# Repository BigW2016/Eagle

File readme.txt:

lfuse:0xE2
hfuse:0xDF
efuse:0xF9

F5mm 5mm Round Ultra Violet UV LED 3.2-3.4V 20mA 395nm - 400nm For DIY
Plastic Nylon Hex Column M3*12mm
Plastic Screw M3*6mm
Plastic Knob for Rotary Taper Potentiometer Hole 6mm - drilled for 6mm

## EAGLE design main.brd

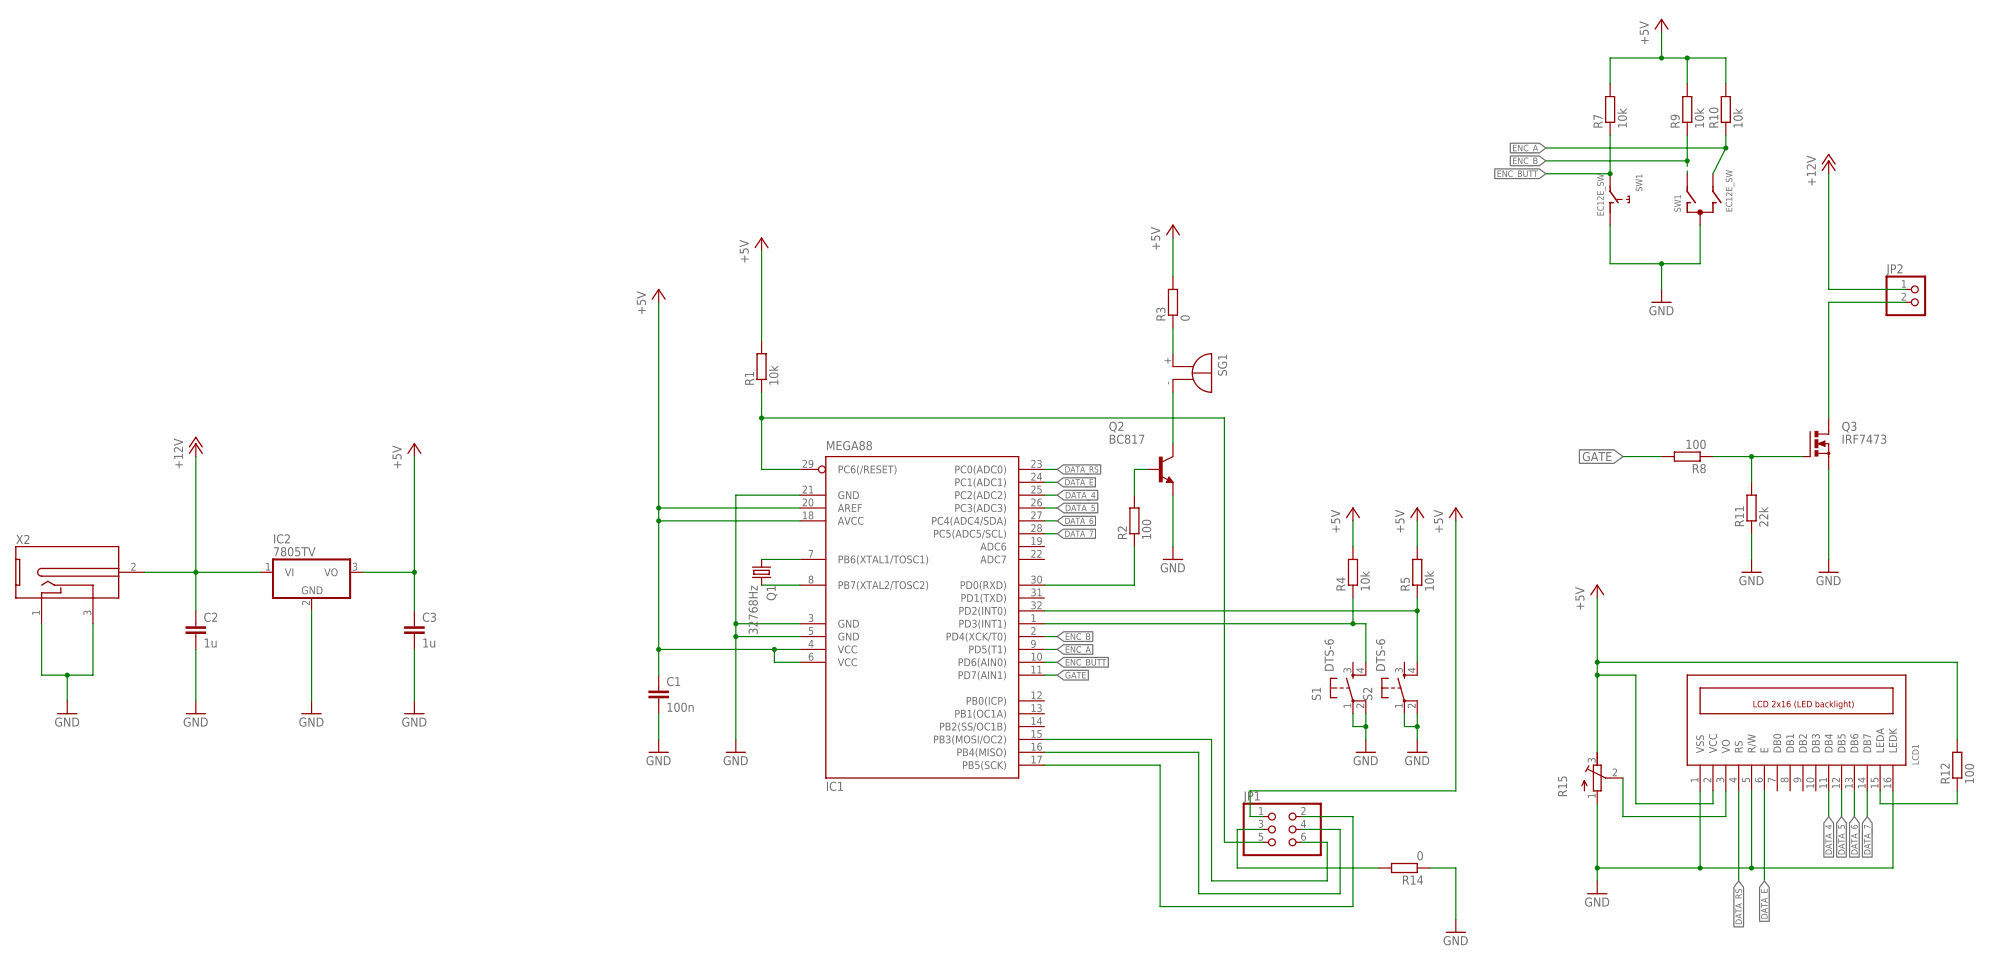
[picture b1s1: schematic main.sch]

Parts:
C1: 100n; C1206K
C2, C3: 1u; C1206K
IC1: MEGA88; TQFP32-08
IC2: 7805TV; TO220V
JP1: PINHD-2X3; 2X03
JP2: PINHD-1X2; 1X02
LCD1: LCD_2X16_SIL; HY-1602F
Q1: 32768Hz; TC38H
Q2: BC817; SOT23-BEC
Q3: IRF7473; SO-08
R1, R4, R5, R7, R9, R10: 10k; R1206
R2, R8, R12: 100; R1206
R3, R14: 0; R1206
R11: 22k; R1206
R15: R-TRIMM3296W; RTRIM3296W
S1, S2: DTS-6
SG1: BMT1205XH7.5
SW1: EC12E_SW; ALPS_EC12E_SW
X2: DC-2.5MM-5MM; DC-21MM

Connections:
+5V: C1.1, C3.1, IC1.4 (VCC), IC1.6 (VCC), IC1.18 (AVCC), IC1.20 (AREF), IC2.3 (VO), JP1.1, LCD1.2 (VCC), R1.2, R3.2, R4.2, R5.2, R7.2, R9.2, R10.2, R12.2, R15.3 (E)
+12V: C2.1, IC2.1 (VI), JP2.1, X2.2 (3)
DATA_4: IC1.25 (PC2(ADC2)), LCD1.11 (DB4)
DATA_5: IC1.26 (PC3(ADC3)), LCD1.12 (DB5)
DATA_6: IC1.27 (PC4(ADC4/SDA)), LCD1.13 (DB6)
DATA_7: IC1.28 (PC5(ADC5/SCL)), LCD1.14 (DB7)
DATA_E: IC1.24 (PC1(ADC1)), LCD1.6 (E)
DATA_RS: IC1.23 (PC0(ADC0)), LCD1.4 (RS)
ENC_A: IC1.9 (PD5(T1)), R10.1, SW1.B
ENC_B: IC1.2 (PD4(XCK/T0)), R9.1, SW1.A
ENC_BUTT: IC1.10 (PD6(AIN0)), R7.1, SW1.E (BUTT)
GATE: IC1.11 (PD7(AIN1)), R8.2
GND: C1.2, C2.2, C3.2, IC1.3 (GND), IC1.5 (GND), IC1.21 (GND), IC2.2 (GND), LCD1.1 (VSS), LCD1.5 (R/W), LCD1.16 (LEDK), Q2.E, Q3.1 (S), Q3.2 (S), Q3.3 (S), R11.1, R14.1, R15.1 (A), S1.1, S1.2, S2.1, S2.2, SW1.C, SW1.GND@1 (BUTT_GND), X2.1, X2.3 (2)
unnamed: IC1.17 (PB5(SCK)), JP1.2
unnamed: JP1.3, R14.2
unnamed: IC1.15 (PB3(MOSI/OC2)), JP1.6
unnamed: Q3.4 (G), R8.1, R11.2
unnamed: IC1.16 (PB4(MISO)), JP1.4
unnamed: IC1.29 (PC6(/RESET)), JP1.5, R1.1
unnamed: IC1.30 (PD0(RXD)), R2.1
unnamed: Q2.C, SG1.-
unnamed: Q2.B, R2.2
unnamed: R3.1, SG1.+
unnamed: JP2.2, Q3.5 (D), Q3.6 (D), Q3.7 (D), Q3.8 (D)
unnamed: IC1.7 (PB6(XTAL1/TOSC1)), Q1.1
unnamed: IC1.8 (PB7(XTAL2/TOSC2)), Q1.2
unnamed: IC1.32 (PD2(INT0)), R5.1, S2.4
unnamed: IC1.1 (PD3(INT1)), R4.1, S1.4
unnamed: LCD1.3 (VO), R15.2 (S)
unnamed: LCD1.15 (LEDA), R12.1

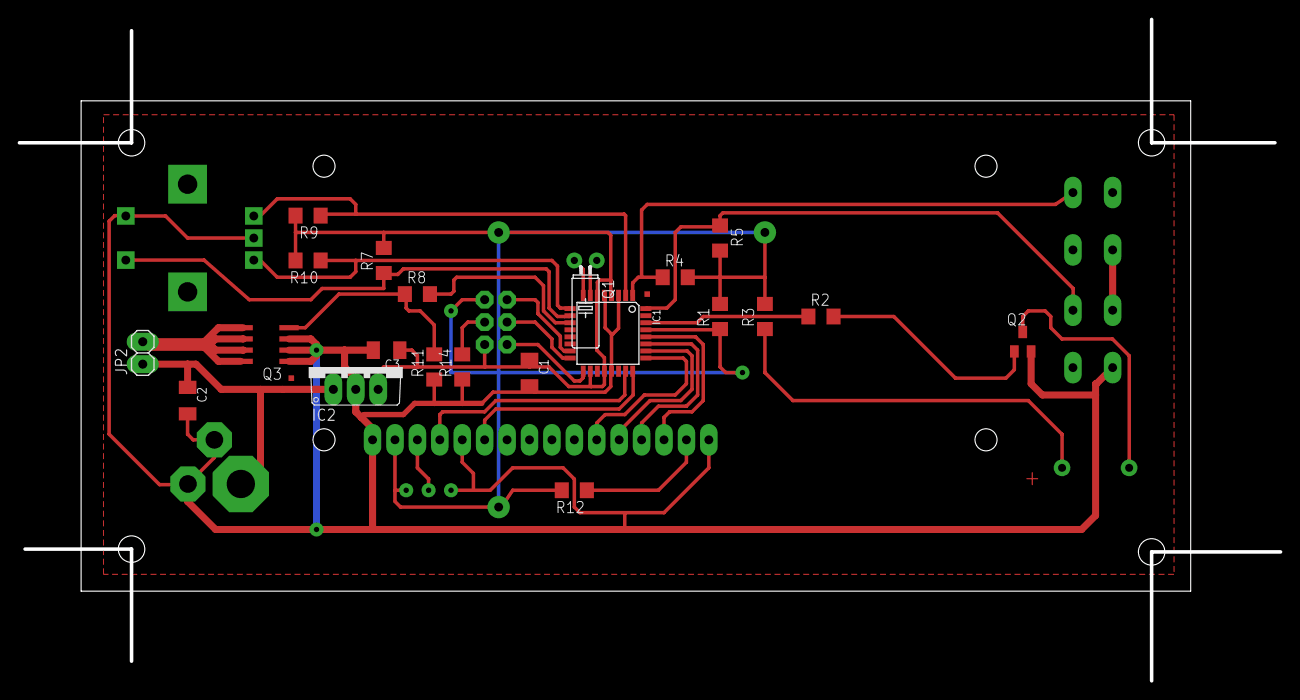
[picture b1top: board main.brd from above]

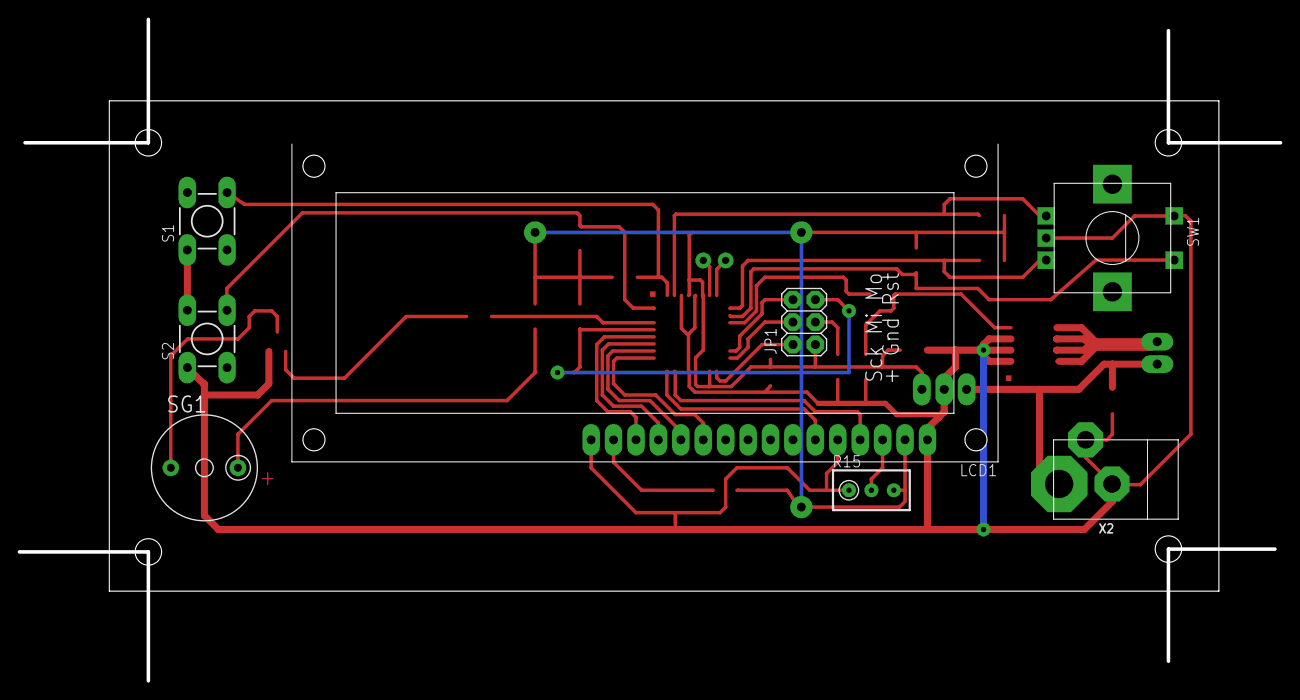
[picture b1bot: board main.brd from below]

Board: 2 copper layers, 142.9 x 74.9 mm, 29 parts (8 on the bottom side), 30 nets.

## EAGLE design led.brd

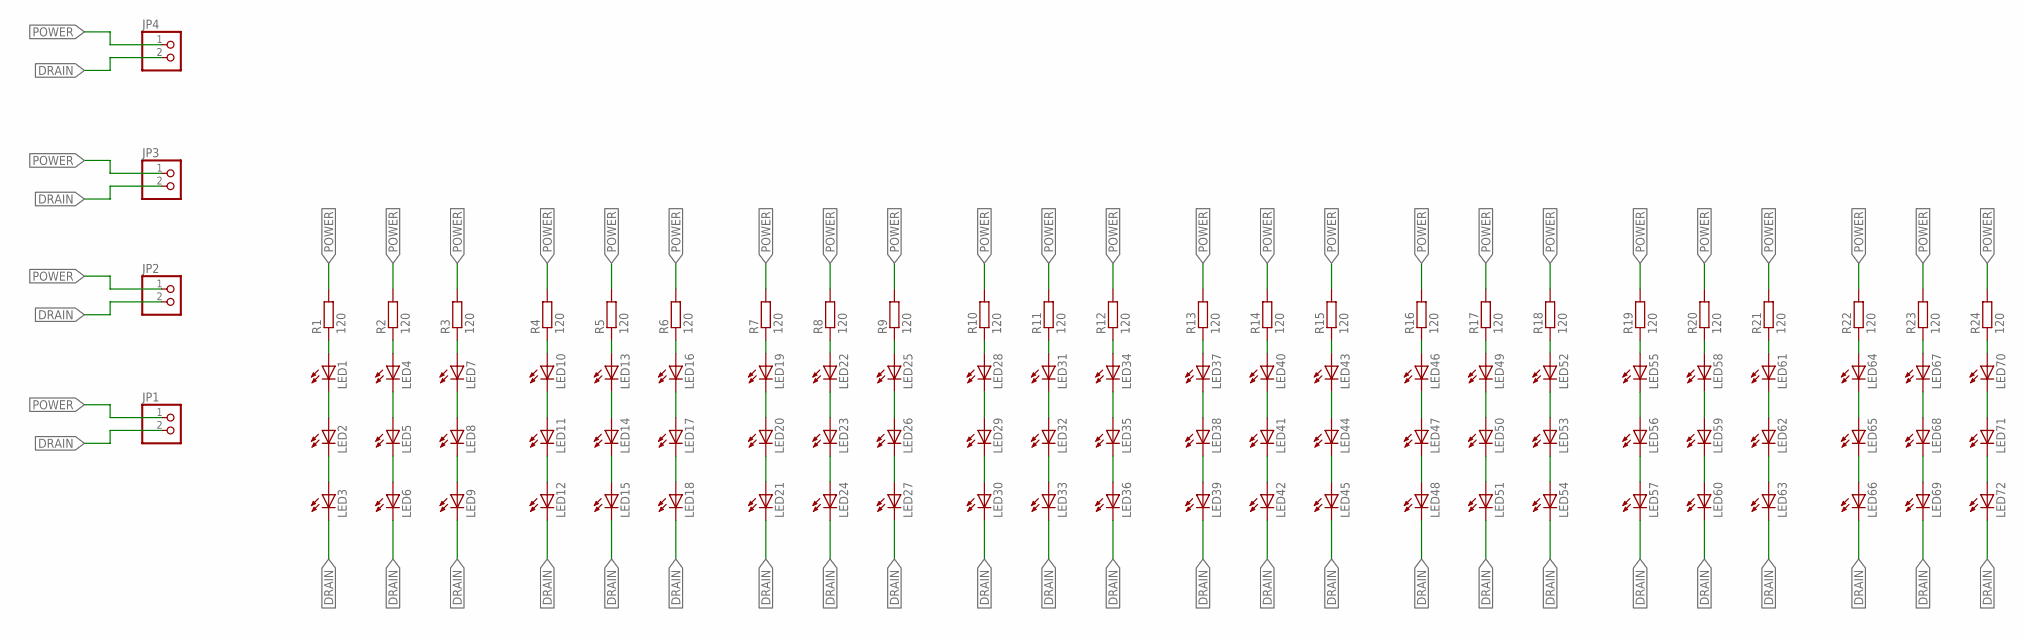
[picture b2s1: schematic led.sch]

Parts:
JP1, JP2, JP3, JP4: PINHD-1X2; 1X02
LED1, LED2, LED3, LED4, LED5, LED6, LED7, LED8, LED9, LED10, LED11, LED12, LED13, LED14, LED15, LED16, LED17, LED18, LED19, LED20, LED21, LED22, LED23, LED24, LED25, LED26, LED27, LED28, LED29, LED30, LED31, LED32, LED33, LED34, LED35, LED36, LED37, LED38, LED39, LED40, LED41, LED42, LED43, LED44, LED45, LED46, LED47, LED48, LED49, LED50, LED51, LED52, LED53, LED54, LED55, LED56, LED57, LED58, LED59, LED60, LED61, LED62, LED63, LED64, LED65, LED66, LED67, LED68, LED69, LED70, LED71, LED72: LED5MM
R1, R2, R3, R4, R5, R6, R7, R8, R9, R10, R11, R12, R13, R14, R15, R16, R17, R18, R19, R20, R21, R22, R23, R24: 120; R0805

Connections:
DRAIN: JP1.2, JP2.2, JP3.2, JP4.2, LED3.K (C), LED6.K (C), LED9.K (C), LED12.K (C), LED15.K (C), LED18.K (C), LED21.K (C), LED24.K (C), LED27.K (C), LED30.K (C), LED33.K (C), LED36.K (C), LED39.K (C), LED42.K (C), LED45.K (C), LED48.K (C), LED51.K (C), LED54.K (C), LED57.K (C), LED60.K (C), LED63.K (C), LED66.K (C), LED69.K (C), LED72.K (C)
unnamed: LED2.K (C), LED3.A
unnamed: LED1.K (C), LED2.A
unnamed: LED1.A, R1.1
unnamed: LED5.K (C), LED6.A
unnamed: LED4.K (C), LED5.A
unnamed: LED4.A, R2.1
unnamed: LED8.K (C), LED9.A
unnamed: LED7.K (C), LED8.A
unnamed: LED7.A, R3.1
unnamed: LED11.K (C), LED12.A
unnamed: LED10.K (C), LED11.A
unnamed: LED10.A, R4.1
unnamed: LED14.K (C), LED15.A
unnamed: LED13.K (C), LED14.A
unnamed: LED13.A, R5.1
unnamed: LED17.K (C), LED18.A
unnamed: LED16.K (C), LED17.A
unnamed: LED16.A, R6.1
unnamed: LED20.K (C), LED21.A
unnamed: LED19.K (C), LED20.A
unnamed: LED19.A, R7.1
unnamed: LED23.K (C), LED24.A
unnamed: LED22.K (C), LED23.A
unnamed: LED22.A, R8.1
unnamed: LED26.K (C), LED27.A
unnamed: LED25.K (C), LED26.A
unnamed: LED25.A, R9.1
unnamed: LED29.K (C), LED30.A
unnamed: LED28.K (C), LED29.A
unnamed: LED28.A, R10.1
unnamed: LED32.K (C), LED33.A
unnamed: LED31.K (C), LED32.A
unnamed: LED31.A, R11.1
unnamed: LED35.K (C), LED36.A
unnamed: LED34.K (C), LED35.A
unnamed: LED34.A, R12.1
unnamed: LED38.K (C), LED39.A
unnamed: LED37.K (C), LED38.A
unnamed: LED37.A, R13.1
unnamed: LED41.K (C), LED42.A
unnamed: LED40.K (C), LED41.A
unnamed: LED40.A, R14.1
unnamed: LED44.K (C), LED45.A
unnamed: LED43.K (C), LED44.A
unnamed: LED43.A, R15.1
unnamed: LED47.K (C), LED48.A
unnamed: LED46.K (C), LED47.A
unnamed: LED46.A, R16.1
unnamed: LED50.K (C), LED51.A
unnamed: LED49.K (C), LED50.A
unnamed: LED49.A, R17.1
unnamed: LED53.K (C), LED54.A
unnamed: LED52.K (C), LED53.A
unnamed: LED52.A, R18.1
unnamed: LED56.K (C), LED57.A
unnamed: LED55.K (C), LED56.A
unnamed: LED55.A, R19.1
unnamed: LED59.K (C), LED60.A
unnamed: LED58.K (C), LED59.A
unnamed: LED58.A, R20.1
unnamed: LED62.K (C), LED63.A
unnamed: LED61.K (C), LED62.A
unnamed: LED61.A, R21.1
unnamed: LED65.K (C), LED66.A
unnamed: LED64.K (C), LED65.A
unnamed: LED64.A, R22.1
unnamed: LED68.K (C), LED69.A
unnamed: LED67.K (C), LED68.A
unnamed: LED67.A, R23.1
unnamed: LED71.K (C), LED72.A
unnamed: LED70.K (C), LED71.A
unnamed: LED70.A, R24.1
POWER: JP1.1, JP2.1, JP3.1, JP4.1, R1.2, R2.2, R3.2, R4.2, R5.2, R6.2, R7.2, R8.2, R9.2, R10.2, R11.2, R12.2, R13.2, R14.2, R15.2, R16.2, R17.2, R18.2, R19.2, R20.2, R21.2, R22.2, R23.2, R24.2

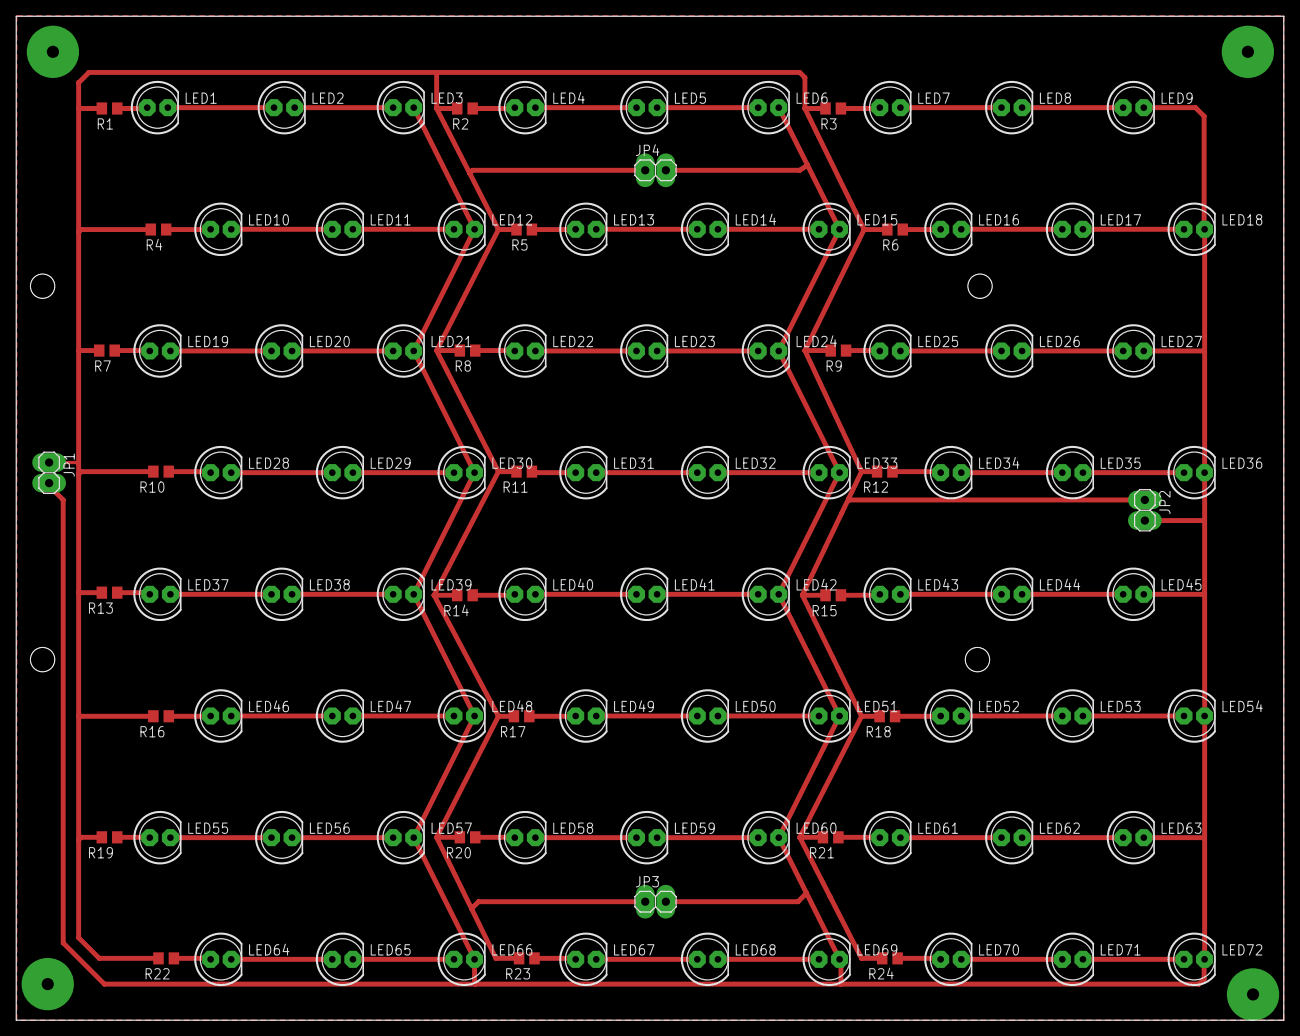
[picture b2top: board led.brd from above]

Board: 2 copper layers, 156.3 x 123.8 mm, 100 parts (0 on the bottom side), 74 nets.

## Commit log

2016-10-29 фоторезист
2016-10-29 контрольный фикс
2016-10-29 и еще
2016-11-19 добавил описание стоек и светодиодов
2016-11-20 добавил описание фьюзов
2016-11-20 добавил дополнительную землю от Moffet
2016-11-20 Заменил AMS1117 на LM7805. От 12В AMS1117 сглючивает и сжигает атмегу
2016-11-21 Чуть пеерделал схему. Добавил файл для печати в типографии с маской и шелкографией
2016-11-26 Исправил ошибку на печатке, не была соединена земля LM7805 и земля Atmega о_О (орел жжет) Исправил печатку маски (правильно выводить tStop)
2017-10-06 орел 8+
